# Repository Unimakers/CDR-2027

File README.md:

# Coupe de France de Robotique 2027 - Unimaker I1/I2

> [!IMPORTANT]
> Ce repo a été créé depuis le template de projet du MakerSpace d'Amiens.
> Les guides d'utilisation du template sont sur le
> [site de documentation du MakerSpace](https://doc.makerspace-amiens.fr/workshops/methodologie-de-projet/).

Ce repo est un site de documentation réalisé par l'équipe des première et deusième années pré-ingénieur de l'école Unilasalle-Amiens, membre de l'association de robotique Unimaker, dans le cadre de leur participation à la Coupe de France de Robotique 2027 (CDR 2027).
Cette documentation sera mise à jour tout au long de l'année à chaque étape du projet.

- **Documentation :** [site du projet](https://unimakers.fr/CDR-2027/) (sources dans [`docs/`](docs/))
- **Fichiers du projet :** [`project/`](project/) (CAO, électronique, code)

## Équipe

### Étudiants de deuxième année

- Ajaz Agbetiafa
- Baptiste Houzelot
- Brett Legret
- Emma Vilain
- Emrick Petit
- Enzo Deviliers
- Gauthier Henriques
- Martin Milon
- Paul Lapeyronnie
- Romain Vantalon
- Samuel Simao

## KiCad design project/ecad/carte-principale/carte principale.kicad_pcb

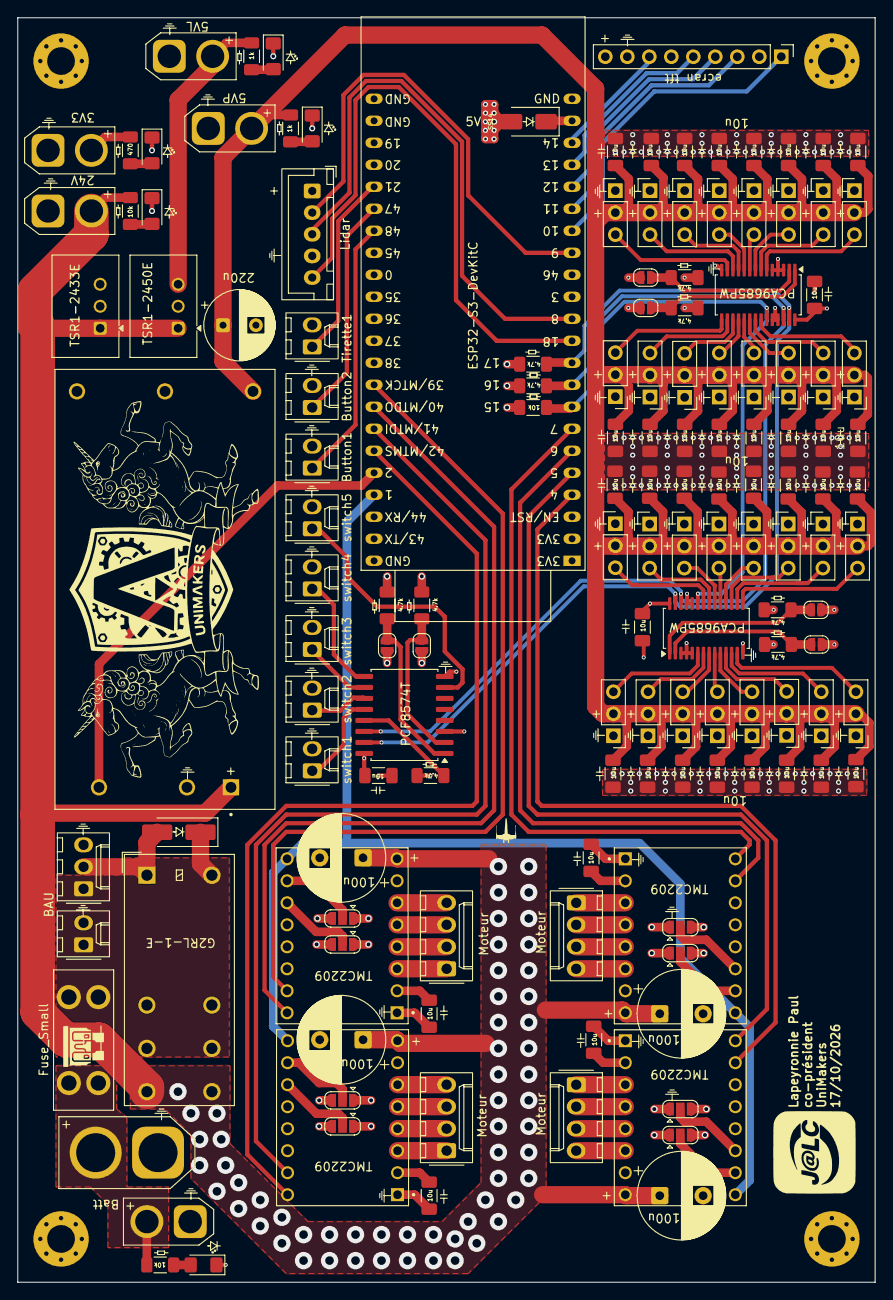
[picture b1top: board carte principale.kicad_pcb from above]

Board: 4 copper layers, 99.0 x 146.0 mm, 151 parts (0 on the bottom side), 106 nets.

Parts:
BAU: Conn_01x02; Molex_KK-254_AE-6410-02A_1x02_P2.54mm_Vertical
Batt: XT60; AMASS_XT60-M_1x02_P7.20mm_Vertical
Button1, Button2: Conn_01x02; Molex_KK-254_AE-6410-02A_1x02_P2.54mm_Vertical
C5, C6, C7, C9: 100u; CP_Radial_D10.0mm_P5.00mm
C12, C13, C14, C16, C17, C18, C19, C21, C22, C24, C25, C26, C27, C28, C29, C30, C31, C32, C33, C34, C35, C36, C37, C38, C39, C40, C41, C42, C43, C44, C45, C46, C47, C48, C49, C50, C51, C52, C53: 10u; C_1206_3216Metric_Pad1.33x1.80mm_HandSolder
C15: 220uF; CP_Radial_D8.0mm_P3.80mm
D1: SS14; D_SMA
D6: D_Small; D_SMA_Handsoldering
DT6, DT8, DT9, DT10, DT11: LED_Small; LED_1206_3216Metric_Pad1.42x1.75mm_HandSolder
F2: Fuse_Small; Fuseholder_Blade_Mini_Keystone_3568
H1, H2, H3, H4: M3; MountingHole_3.2mm_M3_Pad_Via
ICM1: PCF8574T; SOIC-16W_7.5x10.3mm_P1.27mm
J1: ecran tft; PinHeader_1x09_P2.54mm_Vertical
J4, J7, J8, J10: Conn_01x04; Molex_KK-254_AE-6410-04A_1x04_P2.54mm_Vertical
J5: LIDAR; JST_XH_B5B-XH-A_1x05_P2.50mm_Vertical
J6: BAU; Molex_KK-254_AE-6410-03A_1x03_P2.54mm_Vertical
JP1, JP2, JP3, JP4, JP5, JP6, JP16, JP19: SolderJumper_3_Open; SolderJumper-3_P1.3mm_Open_RoundedPad1.0x1.5mm
JP8, JP9, JP10, JP11, JP12, JP13: SolderJumper_2_Open; SolderJumper-2_P1.3mm_Open_RoundedPad1.0x1.5mm
K2: G2RL-1-E; Relay_SPDT_Omron_G2RL-1-E
PS1: TEN_50-2411; CONV_TEN_50-2411
R13, R15, R45: 10k; R_1206_3216Metric_Pad1.30x1.75mm_HandSolder
R14: 470; R_1206_3216Metric_Pad1.30x1.75mm_HandSolder
R16, R17: 1k; R_1206_3216Metric_Pad1.30x1.75mm_HandSolder
R31, R32, R33, R34, R35, R36, R37, R43, R44: 4.7k; R_1206_3216Metric_Pad1.30x1.75mm_HandSolder
Servo1, Servo2, Servo3, Servo4, Servo5, Servo6, Servo7, Servo8, Servo9, Servo10, Servo11, Servo12, Servo13, Servo14, Servo15, Servo16, Servo17, Servo18, Servo19, Servo20, Servo21, Servo22, Servo23, Servo24, Servo25, Servo26, Servo27, Servo28, Servo29, Servo30, Servo31, Servo32: PinHeader_1x03_P2.54mm_Vertical
Tirette1: Conn_01x02; Molex_KK-254_AE-6410-02A_1x02_P2.54mm_Vertical
U1: TSR1-2433E; Converter_DCDC_TRACO_TSR1-xxxxE_THT
U2: TSR1-2450E; Converter_DCDC_TRACO_TSR1-xxxxE_THT
U3, U11: PCA9685PW; TSSOP-28_4.4x9.7mm_P0.65mm
U4: ESP32-S3-DevKitC
U5, U6, U8, U9: TMC2209; MODULE_TMC2209_SILENTSTEPSTICK
XT30_3V3, XT30_5VL1, XT30_5VP1, XT30_24V1, XT30_BATT1: Conn_01x02; AMASS_XT30U-M_1x02_P5.0mm_Vertical
switch1, switch2, switch3, switch4, switch5: Conn_01x02; Molex_KK-254_AE-6410-02A_1x02_P2.54mm_Vertical

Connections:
+3V3: C12.1, C16.1, C18.1, C19.1, C21.1, C22.1, C53.1, ICM1.16 (VDD), J1.2, J1.6, JP1.3 (B), JP2.3 (B), JP3.3 (B), JP4.3 (B), JP5.3 (B), JP6.3 (B), JP8.1 (A), JP9.1 (A), JP10.1 (A), JP11.1 (A), JP12.1 (A), JP13.1 (A), JP16.3 (B), JP19.3 (B), R14.1, R37.1, R43.1, R44.1, R45.1, U1.3 (Vout), U3.28 (VDD), U5.2 (VIO), U6.2 (VIO), U8.2 (VIO), U9.2 (VIO), U11.28 (VDD), XT30_3V3.2
+5VL: D1.2 (A), J1.9, J5.1, R16.1, U2.3 (Vout), XT30_5VL1.2
+5VP: C13.1, C14.1, C15.1, C17.1, C24.1, C25.1, C26.1, C27.1, C28.1, C29.1, C30.1, C31.1, C32.1, C33.1, C34.1, C35.1, C36.1, C37.1, C38.1, C39.1, C40.1, C41.1, C42.1, C43.1, C44.1, C45.1, C46.1, C47.1, C48.1, C49.1, C50.1, C51.1, C52.1, PS1.4 (+VOUT), R17.1, Servo1.2, Servo2.2, Servo3.2, Servo4.2, Servo5.2, Servo6.2, Servo7.2, Servo8.2, Servo9.2, Servo10.2, Servo11.2, Servo12.2, Servo13.2, Servo14.2, Servo15.2, Servo16.2, Servo17.2, Servo18.2, Servo19.2, Servo20.2, Servo21.2, Servo22.2, Servo23.2, Servo24.2, Servo25.2, Servo26.2, Servo27.2, Servo28.2, Servo29.2, Servo30.2, Servo31.2, Servo32.2, XT30_5VP1.2
+24V: C5.1, C6.1, C7.1, C9.1, K2.14, PS1.1 (+VIN(VCC)), R15.1, U1.1 (Vin), U2.1 (Vin), U5.8 (VM), U6.8 (VM), U8.8 (VM), U9.8 (VM), XT30_24V1.2
+BATT: Batt.2, F2.1, R13.1, XT30_BATT1.2
/En driver: U4.41 (GPIO1/ADC1_CH0), U5.16 (~EN), U6.16 (~EN), U8.16 (~EN), U9.16 (~EN)
/RX: J5.3, U4.12 (GPIO8/ADC1_CH7)
/TX: J5.2, U4.15 (GPIO9/ADC1_CH8)
/bu 1: Button1.1, U4.29 (GPIO48)
/bu 2: Button2.1, U4.28 (GPIO47)
/cs: J1.7, U4.20 (GPIO14/ADC2_CH3)
/dc: J1.5, U4.19 (GPIO13/ADC2_CH2)
/oe: R45.2, U3.23 (~OE), U4.8 (GPIO15/ADC2_CH4/32K_P), U11.23 (~OE)
/pwm: J5.5, U4.11 (GPIO18/ADC2_CH7)
/sck: J1.3, U4.17 (GPIO11/ADC2_CH0)
/sdi: J1.4, U4.18 (GPIO12/ADC2_CH1)
/sdo: J1.1, U4.16 (GPIO10/ADC1_CH9)
/sw1: ICM1.12 (P7), switch1.1
/sw2: ICM1.11 (P6), switch2.1
/sw3: ICM1.10 (P5), switch3.1
/sw4: ICM1.9 (P4), switch4.1
/sw5: ICM1.7 (P3), switch5.1
/tir: Tirette1.1 (Pin_1_1), U4.27 (GPIO21)
DIR 1: U4.39 (GPIO42/MTMS), U5.9 (DIR)
DIR 2: U4.5 (GPIO5/ADC1_CH4), U6.9 (DIR)
DIR 3: U4.37 (GPIO40/MTDO), U8.9 (DIR)
DIR 4: U4.7 (GPIO7/ADC1_CH6), U9.9 (DIR)
En5VP: PS1.3 (ON/OFF), U4.40 (GPIO2/ADC1_CH1)
GND: BAU.2, Batt.1, Button1.2, Button2.2, C5.2, C6.2, C7.2, C9.2, C12.2, C13.2, C14.2, C15.2, C16.2, C17.2, C18.2, C19.2, C21.2, C22.2, C24.2, C25.2, C26.2, C27.2, C28.2, C29.2, C30.2, C31.2, C32.2, C33.2, C34.2, C35.2, C36.2, C37.2, C38.2, C39.2, C40.2, C41.2, C42.2, C43.2, C44.2, C45.2, C46.2, C47.2, C48.2, C49.2, C50.2, C51.2, C52.2, C53.2, DT6.1 (K), DT8.1 (K), DT9.1 (K), DT10.1 (K), DT11.1 (K), H1.1 (1_1), H2.1 (1_1), H3.1 (1_1), H4.1 (1_1), ICM1.3 (A2), ICM1.8 (GND), J1.8, J5.4, J6.3, JP1.1 (A), JP2.1 (A), JP3.1 (A), JP4.1 (A), JP5.1 (A), JP6.1 (A), JP16.1 (A), JP19.1 (A), PS1.2 (-VIN(GND)), PS1.5 (-VOUT), R31.2, R32.2, R33.2, R34.2, R35.2, R36.2, Servo1.1, Servo2.1, Servo3.1, Servo4.1, Servo5.1, Servo6.1, Servo7.1, Servo8.1, Servo9.1, Servo10.1, Servo11.1, Servo12.1, Servo13.1, Servo14.1, Servo15.1, Servo16.1, Servo17.1, Servo18.1, Servo19.1, Servo20.1, Servo21.1, Servo22.1, Servo23.1, Servo24.1, Servo25.1, Servo26.1, Servo27.1, Servo28.1, Servo29.1, Servo30.1, Servo31.1, Servo32.1, U1.2 (GND), U2.2 (GND), U3.3 (A2), U3.4 (A3), U3.5 (A4), U3.14 (VSS), U3.24 (A5), U3.25 (EXTCLK), U4.22 (GND), U4.23 (GND), U4.24 (GND), U4.44 (GND), U5.1 (GND), U5.7 (GND), U6.1 (GND), U6.7 (GND), U8.1 (GND), U8.7 (GND), U9.1 (GND), U9.7 (GND), U11.3 (A2), U11.4 (A3), U11.5 (A4), U11.14 (VSS), U11.24 (A5), U11.25 (EXTCLK), XT30_3V3.1, XT30_5VL1.1, XT30_5VP1.1, XT30_24V1.1, XT30_BATT1.1, switch1.2, switch2.2, switch3.2, switch4.2, switch5.2
unnamed: BAU.1, D6.1 (K), F2.2, J6.1, K2.11, K2.A2
unnamed: D1.1 (K), U4.21 (5V)
unnamed: D6.2 (A), J6.2, K2.A1
unnamed: DT6.2 (A), R13.2
unnamed: DT8.2 (A), R15.2
unnamed: DT9.2 (A), R14.2
unnamed: DT10.2 (A), R16.2
unnamed: DT11.2 (A), R17.2
unnamed: ICM1.1 (A0), JP12.2 (B), R35.1
unnamed: ICM1.2 (A1), JP13.2 (B), R36.1
unnamed: ICM1.13 (~INT), R37.2
unnamed: J4.1, U5.3 (M1B)
unnamed: J4.2, U5.4 (M1A)
unnamed: J4.3, U5.5 (M2A)
unnamed: J4.4, U5.6 (M2B)
unnamed: J7.1, U6.3 (M1B)
unnamed: J7.2, U6.4 (M1A)
unnamed: J7.3, U6.5 (M2A)
unnamed: J7.4, U6.6 (M2B)
unnamed: J8.1, U8.3 (M1B)
unnamed: J8.2, U8.4 (M1A)
unnamed: J8.3, U8.5 (M2A)
unnamed: J8.4, U8.6 (M2B)
unnamed: J10.1, U9.3 (M1B)
unnamed: J10.2, U9.4 (M1A)
unnamed: J10.3, U9.5 (M2A)
unnamed: J10.4, U9.6 (M2B)
unnamed: JP1.2 (C), U5.15 (MS1)
unnamed: JP2.2 (C), U5.14 (MS2)
unnamed: JP3.2 (C), U6.15 (MS1)
unnamed: JP4.2 (C), U8.15 (MS1)
unnamed: JP5.2 (C), U8.14 (MS2)
unnamed: JP6.2 (C), U9.15 (MS1)
unnamed: JP8.2 (B), R32.1, U3.1 (A0)
unnamed: JP9.2 (B), R31.1, U3.2 (A1)
unnamed: JP10.2 (B), R33.1, U11.1 (A0)
unnamed: JP11.2 (B), R34.1, U11.2 (A1)
unnamed: JP16.2 (C), U6.14 (MS2)
unnamed: JP19.2 (C), U9.14 (MS2)
unnamed: Servo1.3, U3.7 (LED1)
unnamed: Servo2.3, U3.9 (LED3)
unnamed: Servo3.3, U3.11 (LED5)
unnamed: Servo4.3, U3.13 (LED7)
unnamed: Servo5.3, U3.6 (LED0)
unnamed: Servo6.3, U3.8 (LED2)
unnamed: Servo7.3, U3.10 (LED4)
unnamed: Servo8.3, U3.12 (LED6)
unnamed: Servo9.3, U3.16 (LED9)
unnamed: Servo10.3, U3.18 (LED11)
unnamed: Servo11.3, U3.20 (LED13)
unnamed: Servo12.3, U3.22 (LED15)
unnamed: Servo13.3, U3.15 (LED8)
unnamed: Servo14.3, U3.17 (LED10)
unnamed: Servo15.3, U3.19 (LED12)
unnamed: Servo16.3, U3.21 (LED14)
unnamed: Servo17.3, U11.7 (LED1)
unnamed: Servo18.3, U11.9 (LED3)
unnamed: Servo19.3, U11.11 (LED5)
unnamed: Servo20.3, U11.13 (LED7)
unnamed: Servo21.3, U11.16 (LED9)
unnamed: Servo22.3, U11.18 (LED11)
unnamed: Servo23.3, U11.20 (LED13)
unnamed: Servo24.3, U11.22 (LED15)
unnamed: Servo25.3, U11.6 (LED0)
unnamed: Servo26.3, U11.8 (LED2)
unnamed: Servo27.3, U11.10 (LED4)
unnamed: Servo28.3, U11.12 (LED6)
unnamed: Servo29.3, U11.15 (LED8)
unnamed: Servo30.3, U11.17 (LED10)
unnamed: Servo31.3, U11.19 (LED12)
unnamed: Servo32.3, U11.21 (LED14)
SCL: ICM1.14 (SCL), R43.2, U3.26 (SCL), U4.9 (GPIO16/ADC2_CH5/32K_N), U11.26 (SCL)
SDA: ICM1.15 (SDA), R44.2, U3.27 (SDA), U4.10 (GPIO17/ADC2_CH6), U11.27 (SDA)
STEP 1: U4.38 (GPIO41/MTDI), U5.10 (STEP)
STEP 2: U4.4 (GPIO4/ADC1_CH3), U6.10 (STEP)
STEP 3: U4.36 (GPIO39/MTCK), U8.10 (STEP)
STEP 4: U4.6 (GPIO6/ADC1_CH5), U9.10 (STEP)

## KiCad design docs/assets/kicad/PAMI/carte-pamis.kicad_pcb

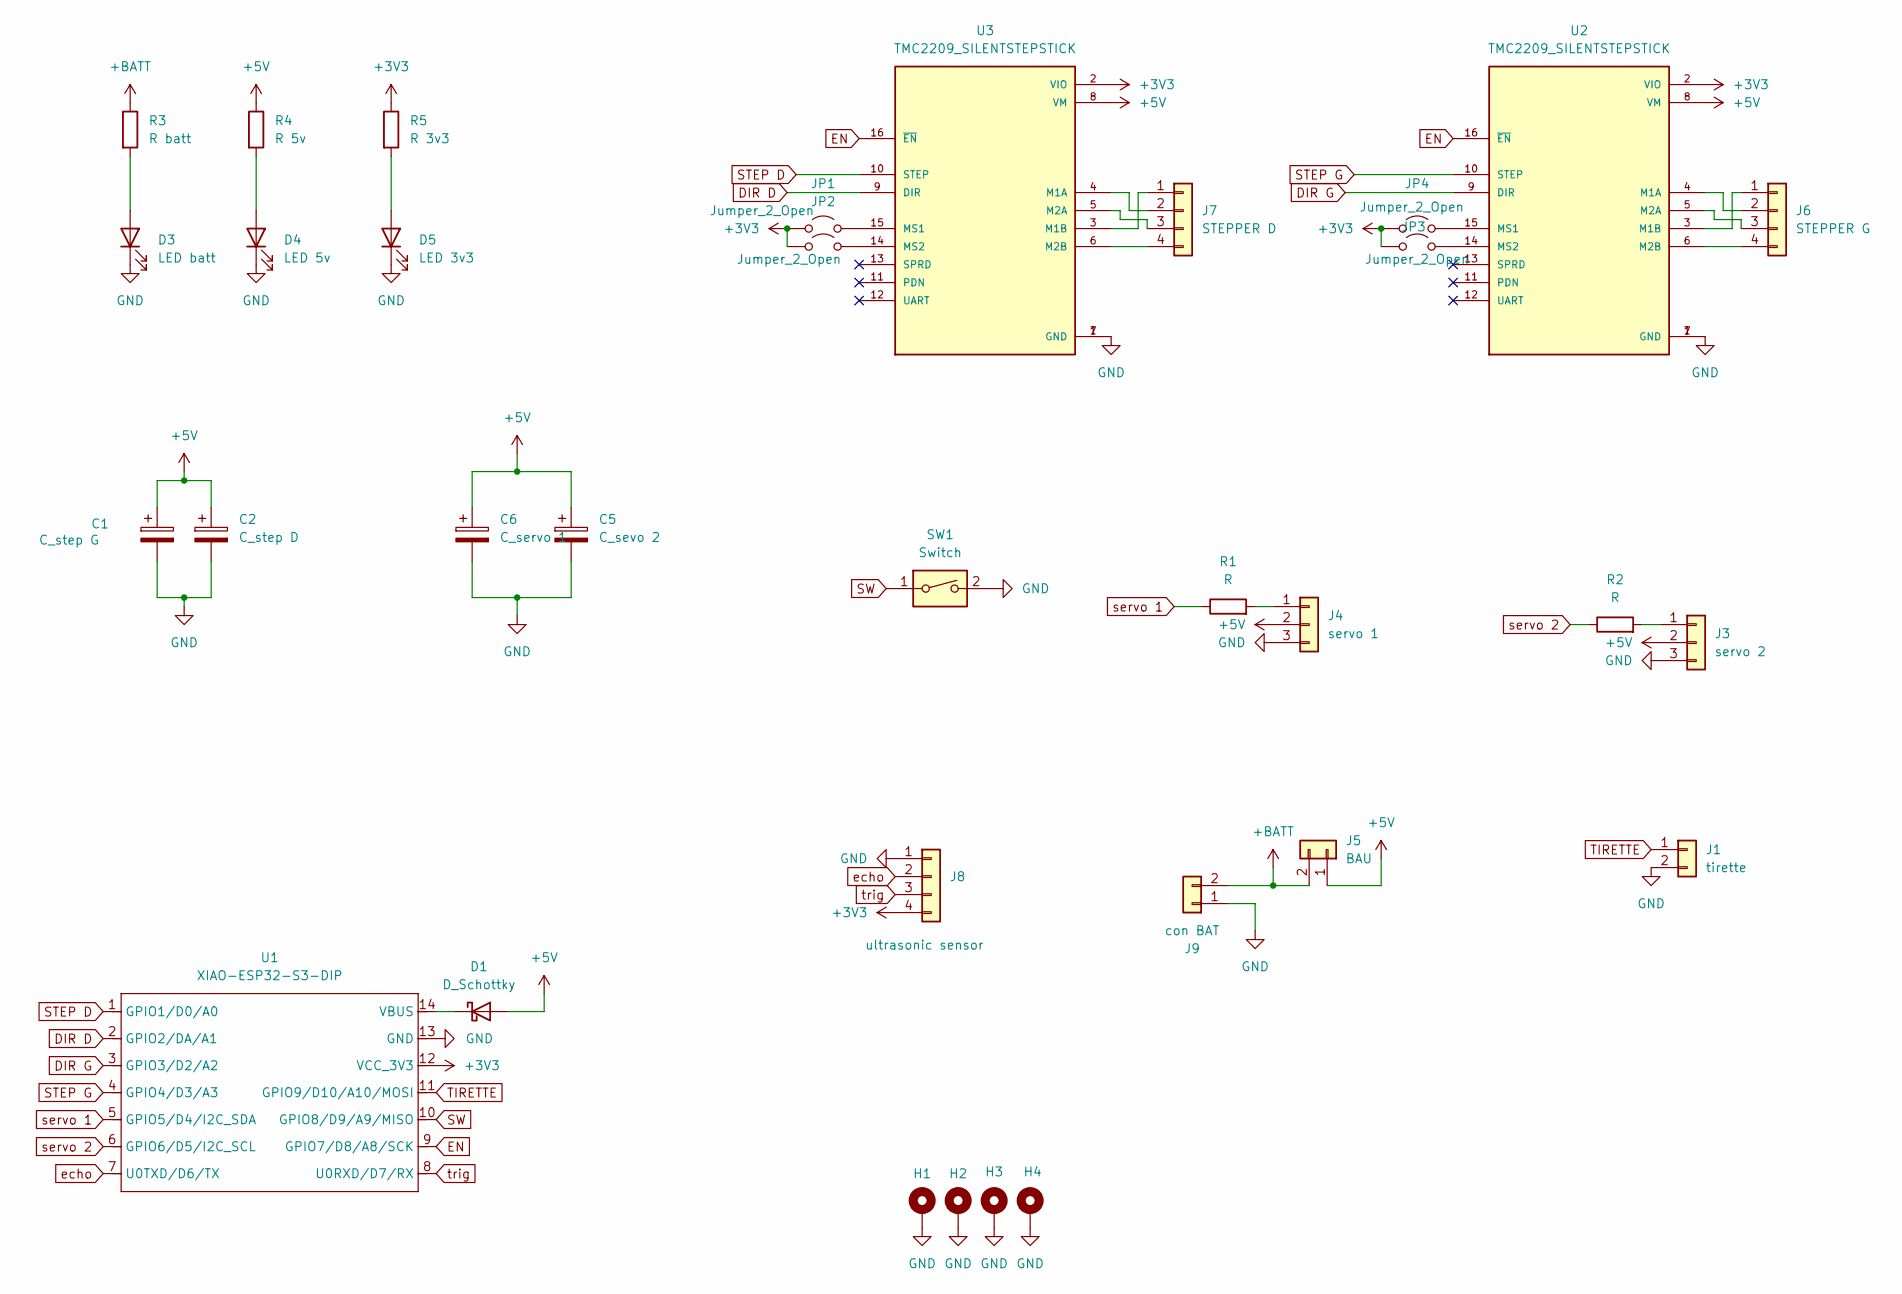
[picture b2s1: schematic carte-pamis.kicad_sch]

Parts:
C1: C_step G; CP_Radial_D6.3mm_P2.50mm
C2: C_step D; CP_Radial_D6.3mm_P2.50mm
C5: C_sevo 2; CP_Radial_D6.3mm_P2.50mm
C6: C_servo 1; CP_Radial_D6.3mm_P2.50mm
D1: D_Schottky; D_A-405_P10.16mm_Horizontal
D3: LED batt; LED_1206_3216Metric_Pad1.42x1.75mm_HandSolder
D4: LED 5v; LED_1206_3216Metric_Pad1.42x1.75mm_HandSolder
D5: LED 3v3; LED_1206_3216Metric_Pad1.42x1.75mm_HandSolder
H1, H2, H3, H4: MountingHole_Pad; MountingHole_3.2mm_M3_Pad_Via
J1: tirette; Molex_KK-254_AE-6410-02A_1x02_P2.54mm_Vertical
J3: servo 2; PinHeader_1x03_P2.54mm_Vertical
J4: servo 1; PinHeader_1x03_P2.54mm_Vertical
J5: BAU; Molex_KK-396_A-41791-0002_1x02_P3.96mm_Vertical
J6: STEPPER G; Molex_KK-254_AE-6410-04A_1x04_P2.54mm_Vertical
J7: STEPPER D; Molex_KK-254_AE-6410-04A_1x04_P2.54mm_Vertical
J8: ultrasonic sensor; PinSocket_1x04_P2.54mm_Vertical
J9: con BAT; AMASS_XT30U-M_1x02_P5.0mm_Vertical
JP1, JP2, JP3, JP4: Jumper_2_Open; SolderJumper-2_P1.3mm_Open_RoundedPad1.0x1.5mm
R1: R; R_1206_3216Metric_Pad1.30x1.75mm_HandSolder
R2: R; C_1206_3216Metric_Pad1.33x1.80mm_HandSolder
R3: R batt; R_1206_3216Metric_Pad1.30x1.75mm_HandSolder
R4: R 5v; R_1206_3216Metric_Pad1.30x1.75mm_HandSolder
R5: R 3v3; R_1206_3216Metric_Pad1.30x1.75mm_HandSolder
SW1: Switch; SW_DIP_SPSTx01_Slide_9.78x4.72mm_W7.62mm_P2.54mm
U1: XIAO-ESP32-S3-DIP; XIAO-ESP32S3-DIP
U2, U3: TMC2209_SILENTSTEPSTICK; MODULE_TMC2209_SILENTSTEPSTICK; PARTREV 1.20

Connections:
+3V3: J8.4, JP1.1 (A), JP2.1 (A), JP3.1 (A), JP4.1 (A), R5.1, U1.12 (VCC_3V3), U2.2 (VIO), U3.2 (VIO)
+5V: C1.1, C2.1, C5.1, C6.1, D1.2 (A), J3.2, J4.2, J5.1, R4.1, U2.8 (VM), U3.8 (VM)
+BATT: J5.2, J9.2, R3.1
DIR D: U1.2 (GPIO2/DA/A1), U3.9 (DIR)
DIR G: U1.3 (GPIO3/D2/A2), U2.9 (DIR)
EN: U1.9 (GPIO7/D8/A8/SCK), U2.16 (~EN), U3.16 (~EN)
GND: C1.2, C2.2, C5.2, C6.2, D3.1 (K), D4.1 (K), D5.1 (K), H1.1, H2.1, H3.1, H4.1, J1.2, J3.3, J4.3, J8.1, J9.1, SW1.2, U1.13 (GND), U2.1 (GND), U2.7 (GND), U3.1 (GND), U3.7 (GND)
unnamed: D1.1 (K), U1.14 (VBUS)
unnamed: D3.2 (A), R3.2
unnamed: D4.2 (A), R4.2
unnamed: D5.2 (A), R5.2
unnamed: J3.1, R2.2
unnamed: J4.1, R1.2
unnamed: J6.1, U2.3 (M1B)
unnamed: J6.2, U2.4 (M1A)
unnamed: J6.3, U2.5 (M2A)
unnamed: J6.4, U2.6 (M2B)
unnamed: J7.1, U3.3 (M1B)
unnamed: J7.2, U3.4 (M1A)
unnamed: J7.3, U3.5 (M2A)
unnamed: J7.4, U3.6 (M2B)
unnamed: JP1.2 (B), U3.15 (MS1)
unnamed: JP2.2 (B), U3.14 (MS2)
unnamed: JP3.2 (B), U2.14 (MS2)
unnamed: JP4.2 (B), U2.15 (MS1)
STEP D: U1.1 (GPIO1/D0/A0), U3.10 (STEP)
STEP G: U1.4 (GPIO4/D3/A3), U2.10 (STEP)
SW: SW1.1, U1.10 (GPIO8/D9/A9/MISO)
TIRETTE: J1.1, U1.11 (GPIO9/D10/A10/MOSI)
echo: J8.2, U1.7 (U0TXD/D6/TX)
servo 1: R1.1, U1.5 (GPIO5/D4/I2C_SDA)
servo 2: R2.1, U1.6 (GPIO9/D5/I2C_SCL)
trig: J8.3, U1.8 (U0RXD/D7/RX)

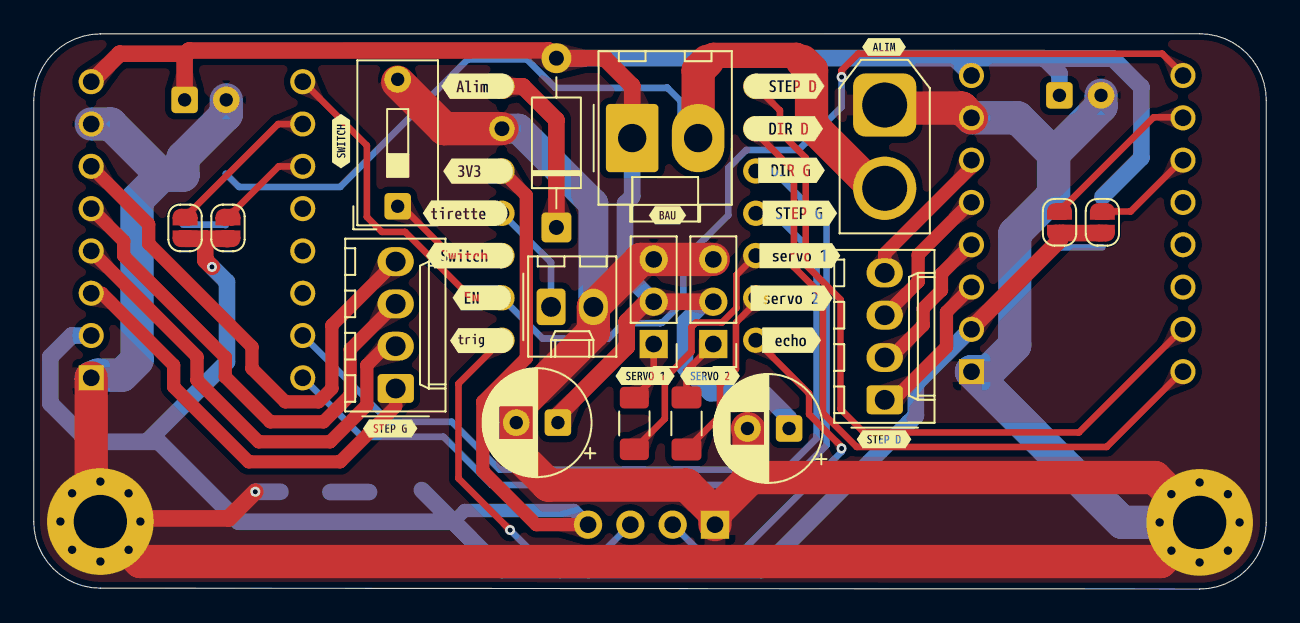
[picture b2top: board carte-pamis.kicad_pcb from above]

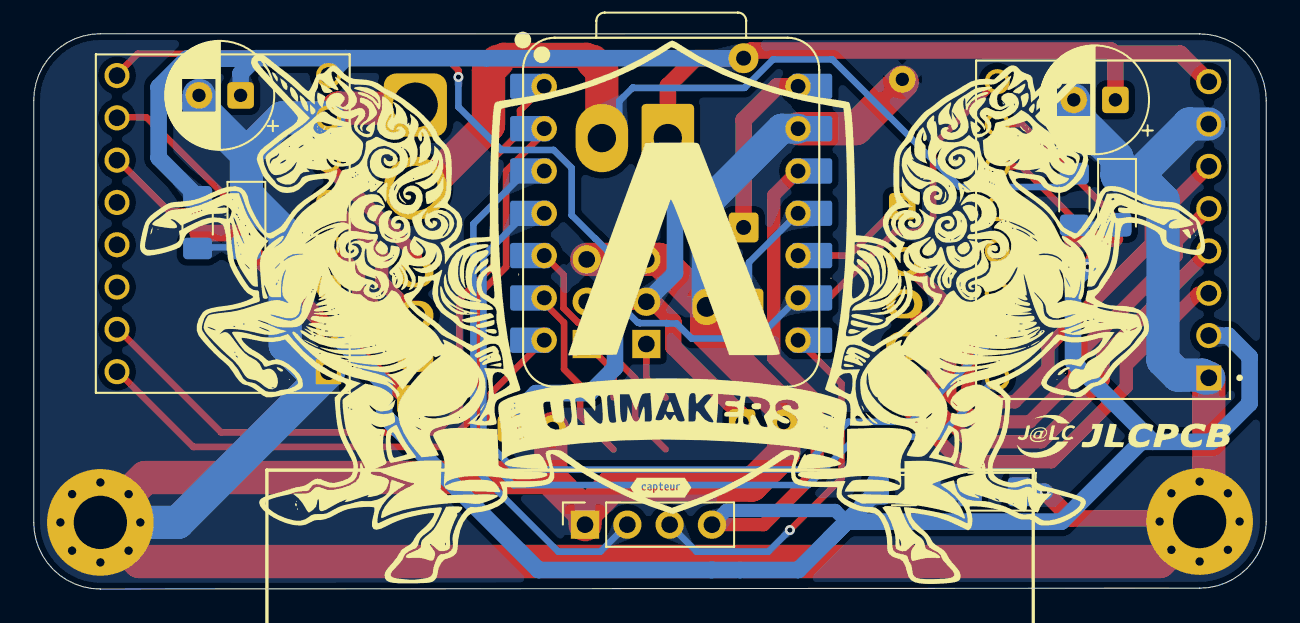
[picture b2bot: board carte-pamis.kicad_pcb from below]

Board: 2 copper layers, 74.0 x 33.3 mm, 52 parts (13 on the bottom side), 33 nets.

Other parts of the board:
kibuzzard-69BD5A4D: G***; kibuzzard-69BD5A4D
kibuzzard-69BD5AEA: G***; kibuzzard-69BD5AEA
kibuzzard-69BD5B6A: G***; kibuzzard-69BD5B6A
kibuzzard-69BD5B57: G***; kibuzzard-69BD5B57
kibuzzard-69BD5B92: G***; kibuzzard-69BD5B92
kibuzzard-69BD5BD3: G***; kibuzzard-69BD5BD3
kibuzzard-69BD5C33: G***; kibuzzard-69BD5C33
kibuzzard-69BD5DD3: G***; kibuzzard-69BD5DD3
kibuzzard-69C3F8DE: G***; kibuzzard-69C3F8DE
kibuzzard-69C3F80C: G***; kibuzzard-69C3F80C
kibuzzard-69C3F81F: G***; kibuzzard-69C3F81F
kibuzzard-69C3F82B: G***; kibuzzard-69C3F82B
kibuzzard-69C3F838: G***; kibuzzard-69C3F838
kibuzzard-69C3F846: G***; kibuzzard-69C3F846
kibuzzard-69C4E0EF: G***; kibuzzard-69C4E0EF
kibuzzard-69C4E14F: G***; kibuzzard-69C4E14F
kibuzzard-69C402F1: G***; kibuzzard-69C402F1
kibuzzard-69C403F5: G***; kibuzzard-69C403F5
kibuzzard-69C4034C: G***; kibuzzard-69C4034C
kibuzzard-69C40313: G***; kibuzzard-69C40313
kibuzzard-69C40336: G***; kibuzzard-69C40336

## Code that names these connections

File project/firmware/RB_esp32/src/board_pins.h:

// Board pinout: exact mirror of the KiCad project ECAD-2026 "body v1"
// (Seeed XIAO ESP32-S3 Plus = X1), its two driver boards "leg v1" (2x TMC2209 each,
// plugged on NP1 and NP2) and the head board "head v1" (plugged on NP3).
// Checked against the PCB nets (body v1.kicad_pcb, carte driver.kicad_pcb).
// Only edit this file when a PCB changes. What each slot is USED for lives in robot_config.h.

#pragma once

#include <stdint.h>

// ---------------------------------------------------------------------------
// I2C bus: PCF8574 of the body (drivers), PCF8574 of the head (switches),
// external PCA9685 modules on the 4 I2C connectors IC1..IC4.
// 4.7k pull-ups to 3V3 on the body (R5, R6) and on the head (R7, R8).
// The PCF8574 is a 100 kHz (standard mode) chip: keep the Wire default clock.
// ---------------------------------------------------------------------------
#define I2C_SDA_PIN 5 // D4
#define I2C_SCL_PIN 6 // D5

// ---------------------------------------------------------------------------
// Stepper drivers: 2 driver boards "leg v1", 2 TMC2209 each, 24V, STEP/DIR on the XIAO,
// ~EN and microstepping (MS1/MS2) on the body PCF8574. UART, DIAG, INDEX not wired.
//
//   slot | body conn. | driver board | motor connector | 2026 robot use
//   -----+------------+--------------+-----------------+---------------
//     0  |    NP1     |  U1          |  J3             | back elevator
//     1  |    NP1     |  U2          |  J2             | LEFT wheel
//     2  |    NP2     |  U1          |  J3             | front elevator
//     3  |    NP2     |  U2          |  J2             | RIGHT wheel
//
// WARNING: on the driver board the nets "STEP 1" and "DIR 1" are swapped on U1
// (net "STEP 1" goes to the DIR pad 9, net "DIR 1" to the STEP pad 10). U2 is right.
// The pins below are the REAL function at the TMC2209, so the swap is already corrected:
// slot 0 STEP = net "DIR 1" (GPIO4), slot 2 STEP = net "DIR 3" (GPIO2).
// (The 2026 firmware used the net names, STEP = GPIO3 / GPIO1, for the elevators: if an
// elevator does not move, swap STEP_1/DIR_1 or STEP_3/DIR_3 here. The wheels are on U2,
// not affected, and their pins are the ones validated in 2026.)
// ---------------------------------------------------------------------------
#define STEPPER_SLOT_COUNT 4

#define STEP_1_PIN 4  // net "DIR 1"  (D3)   -> NP1 U1 STEP
#define DIR_1_PIN 3   // net "STEP 1" (D2)   -> NP1 U1 DIR
#define STEP_2_PIN 40 // net "STEP 2" (D13)  -> NP1 U2 STEP
#define DIR_2_PIN 10  // net "DIR 2"  (D16)  -> NP1 U2 DIR
#define STEP_3_PIN 2  // net "DIR 3"  (D1)   -> NP2 U1 STEP
#define DIR_3_PIN 1   // net "STEP 3" (D0)   -> NP2 U1 DIR
#define STEP_4_PIN 38 // net "STEP 4" (D11)  -> NP2 U2 STEP
#define DIR_4_PIN 39  // net "DIR 4"  (D12)  -> NP2 U2 DIR

// Driver board of each slot: both TMC2209 of a board share ~EN, MS1 and MS2.
#define DRIVER_BOARD_COUNT 2
const uint8_t STEPPER_SLOT_BOARD[STEPPER_SLOT_COUNT] = {0, 0, 1, 1}; // slot -> board (0 = NP1, 1 = NP2)

// ---------------------------------------------------------------------------
// PCF8574T ICM1 on the body: ~EN and MS1/MS2 of the 2 driver boards.
// Address = 0x20 + (A2 A1 A0) for a PCF8574T (0x38 + ... would be a PCF8574AT).
// A0..A2 have a pull-down (R1..R3) and a solder jumper to 3V3 (JP1..JP3): 0x20 with no jumper.
// ~INT has a 4.7k pull-up (R4) but is not wired to the XIAO.
//
// At power-on every PCF pin is HIGH (weak pull-up): ~EN = 1 -> drivers disabled,
// MS1 = MS2 = 1 -> 1/16 microstep, until steppersBegin() writes the real values.
//
//   PCF bit | NP pin | driver board signal
//   --------+--------+--------------------
//     P3    | NP1-1  | board 0 ~EN
//     P2    | NP1-2  | board 0 MS1
//     P1    | NP1-3  | (not connected on the driver board)
//     P0    | NP1-4  | board 0 MS2
//     P4    | NP2-1  | board 1 ~EN
//     P5    | NP2-2  | board 1 MS1
//     P6    | NP2-3  | (not connected on the driver board)
//     P7    | NP2-4  | board 1 MS2
// ---------------------------------------------------------------------------
#define PCF_DRIVERS_ADDR 0x20

const uint8_t DRIVER_EN_PCF_BIT[DRIVER_BOARD_COUNT] = {3, 4};
const uint8_t DRIVER_MS1_PCF_BIT[DRIVER_BOARD_COUNT] = {2, 5};
const uint8_t DRIVER_MS2_PCF_BIT[DRIVER_BOARD_COUNT] = {0, 7};
#define DRIVERS_EN_ACTIVE_LOW true

// TMC2209 standalone microstepping (MS1 / MS2 levels):
//   MS1=0 MS2=0 -> 8   |   MS1=1 MS2=0 -> 2   |   MS1=0 MS2=1 -> 4   |   MS1=1 MS2=1 -> 16

// ---------------------------------------------------------------------------
// Power
// ---------------------------------------------------------------------------
#define EN_5VP_PIN 13 // "En5VP" (D17): ON/OFF of the 5VP converter PS1 (servos/pumps)

// ---------------------------------------------------------------------------
// PCA9685 PWM drivers: no longer on the body, external modules on the I2C
// connectors IC1..IC4. Address = 0x40 + jumpers of the module.
// 0x70 is the PCA9685 "all call" address (enabled at power-on): never give it to a chip.
// ---------------------------------------------------------------------------
#define PCA_COUNT 2
#define PCA_CHANNEL_COUNT 16 // outputs per PCA9685

#define PCA_1_ADDR 0x40
#define PCA_2_ADDR 0x41

// ~OE of the PCA modules is not wired to the XIAO (module pull-down = outputs on)
#define PCA_OE_PIN -1

static_assert(PCA_1_ADDR == -1 || PCA_2_ADDR == -1 || PCA_1_ADDR != PCA_2_ADDR,
              "Both PCA9685 have the same I2C address, check the module jumpers");
static_assert(PCA_1_ADDR != 0x70 && PCA_2_ADDR != 0x70,
              "0x70 is the PCA9685 all-call address, choose another one");

// Actuator "connectors" 1..32 = PCA 1 outputs 0..15 then PCA 2 outputs 0..15
// (straight mapping on the external modules, unlike the interleaved old main board).
#define ACTUATOR_CONNECTOR_COUNT (PCA_COUNT * PCA_CHANNEL_COUNT)
const uint8_t ACTUATOR_PCA_CHANNEL[PCA_CHANNEL_COUNT] = {0, 1, 2, 3, 4, 5, 6, 7, 8, 9, 10, 11, 12, 13, 14, 15};

// ---------------------------------------------------------------------------
// Head board (NP3 "IHM + Lidar"): PCF8574T ICM1 with 4 switch connectors J1..J4.
// Same chip and same jumper circuit as the body PCF: with no jumper BOTH PCF answer
// on 0x20 and the bus does not work. Solder JP1 (A0) on the head -> 0x21.
// Switch contact to GND. Quasi-bidirectional pins: write 1 before reading, closed = 0.
// P4..P7 are not connected.
// ---------------------------------------------------------------------------
#define PCF_HEAD_ADDR 0x21

#define SWITCH_COUNT 4
const uint8_t SWITCH_PCF_BIT[SWITCH_COUNT] = {0, 1, 2, 3}; // J1..J4 -> P0..P3

static_assert(PCF_DRIVERS_ADDR != PCF_HEAD_ADDR,
              "Both PCF8574 have the same I2C address: solder JP1 on the head board");
static_assert(PCF_DRIVERS_ADDR != PCA_1_ADDR && PCF_DRIVERS_ADDR != PCA_2_ADDR &&
              PCF_HEAD_ADDR != PCA_1_ADDR && PCF_HEAD_ADDR != PCA_2_ADDR,
              "A PCF8574 shares its I2C address with a PCA9685");

// ---------------------------------------------------------------------------
// Inputs on the XIAO, through the head board (contact to GND: use INPUT_PULLUP)
// ---------------------------------------------------------------------------
#define TIRETTE_PIN 12     // "tir" (D18), head J6
#define TEAM_SWITCH_PIN 11 // "TSW" (D19), head J7

// ---------------------------------------------------------------------------
// WS2812B RGB LEDs on the head (D11 -> D12 chained), 5VL powered
// ---------------------------------------------------------------------------
#define RGB_LED_PIN 7 // "LED" (D8)
#define RGB_LED_COUNT 2

// ---------------------------------------------------------------------------
// LIDAR LD06 on head J5, UART1 on the XIAO hardware UART pins.
// Serial = native USB CDC on the XIAO, so GPIO43/44 are free for the lidar.
// Always pass the pins: Serial1.begin(LD06_BAUDRATE, SERIAL_8N1, LD06_RX_PIN, LD06_TX_PIN),
// and never call LD06::init(), which uses the defaults.
// ---------------------------------------------------------------------------
#define LD06_UART_NUM 1
// The nets are named from the lidar side: the LD06 data arrives on net "TX" (GPIO43).
// Same as Firmware-CDR2026-MainBot (LIDAR_RX_PIN = TX), validated on the 2026 robot.
#define LD06_RX_PIN 43 // net "TX" (D6): XIAO RX <- LD06 TX (head J5 pin 2)
#define LD06_TX_PIN 44 // net "RX" (D7): XIAO TX -> head J5 pin 3
#define LD06_BAUDRATE 230400
#define LD06_PWM_PIN 8 // "PWM" (D9): motor speed PWM, head J5 pin 5

// ---------------------------------------------------------------------------
// XBee (L1: DOUT, DIN, 3V3, GND) on UART2
// ---------------------------------------------------------------------------
#define XBEE_RX_PIN 41 // "DOUT-xbee" (D14): XIAO RX <- XBee DOUT
#define XBEE_TX_PIN 42 // "DIN-xbee"  (D15): XIAO TX -> XBee DIN

// Free: GPIO9 (D10)

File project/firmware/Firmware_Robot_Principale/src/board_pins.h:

// Board pinout: exact mirror of the final KiCad schematic "carte principale"
// (project/ecad/carte-principale, ESP32-S3-DevKitC-1 = U4).
// Only edit this file when the PCB changes. What each slot is USED for lives in robot_config.h.

#pragma once

#include <stdint.h>

// ---------------------------------------------------------------------------
// Stepper drivers (TMC2209 U5, U6, U8, U9, 24V, STEP/DIR only: UART, DIAG and INDEX not wired)
// Slot index used in robot_config.h = STEP/DIR number on the schematic - 1.
//
//   slot | driver | motor connector | microstep jumpers (MS1 / MS2)
//   -----+--------+-----------------+------------------------------
//     0  |   U5   |       J4        |   JP1 / JP2
//     1  |   U6   |       J7        |   JP3 / JP16
//     2  |   U8   |       J8        |   JP4 / JP5
//     3  |   U9   |       J10       |   JP6 / JP19
// ---------------------------------------------------------------------------
#define STEPPER_SLOT_COUNT 4

#define STEP_1_PIN 41
#define DIR_1_PIN 42
#define STEP_2_PIN 4
#define DIR_2_PIN 5
#define STEP_3_PIN 39
#define DIR_3_PIN 40
#define STEP_4_PIN 6
#define DIR_4_PIN 7

// Shared ~EN of the 4 drivers ("En driver"), active LOW. No pull resistor on the board:
// the line floats from power-on until steppersBegin() drives it.
#define MOTORS_EN_PIN 1
#define MOTORS_EN_ACTIVE_LOW true

// TMC2209 standalone microstepping, set by the solder jumpers (B = 3V3, A = GND):
//   MS1=0 MS2=0 -> 8   |   MS1=1 MS2=0 -> 2   |   MS1=0 MS2=1 -> 4   |   MS1=1 MS2=1 -> 16

// ---------------------------------------------------------------------------
// Power
// ---------------------------------------------------------------------------
#define EN_5VP_PIN 2 // ON/OFF of the 5VP converter PS1 (servos/pumps)

// ---------------------------------------------------------------------------
// I2C bus: the 2 PCA9685 and the PCF8574, 4.7k pull-ups to 3V3 on board (R43, R44)
// The PCF8574 is a 100 kHz (standard mode) chip: keep the Wire default clock, do not
// raise it with Wire.setClock() while the PCF8574 is on the bus.
// ---------------------------------------------------------------------------
#define I2C_SDA_PIN 17
#define I2C_SCL_PIN 16

// ---------------------------------------------------------------------------
// PCA9685 PWM drivers U3 and U11: signal only. The actuators get 5VP + GND from the board.
// ---------------------------------------------------------------------------
#define PCA_COUNT 2
#define PCA_CHANNEL_COUNT 16 // outputs per PCA9685

// Address = 0x40 + (A1 A0). A2..A5 are tied to GND; A0/A1 have a 4.7k pull-down
// and a solder jumper to 3V3. With no jumper soldered both chips answer on 0x40.
//   U3  (PCA 1): A0 = JP8,  A1 = JP9   -> 0x40 with no jumper
//   U11 (PCA 2): A0 = JP10, A1 = JP11  -> 0x41 with JP10 soldered
// 0x70 is the PCA9685 "all call" address (enabled at power-on): never give it to a chip.
#define PCA_1_ADDR 0x40
#define PCA_2_ADDR 0x41

// ~OE of both PCA, active LOW. 10k pull-up (R45): every output is off from
// power-on until actuatorsBegin() drives it LOW.
#define PCA_OE_PIN 15

static_assert(PCA_1_ADDR == -1 || PCA_2_ADDR == -1 || PCA_1_ADDR != PCA_2_ADDR,
              "Both PCA9685 have the same I2C address, check the solder jumpers");
static_assert(PCA_1_ADDR != 0x70 && PCA_2_ADDR != 0x70,
              "0x70 is the PCA9685 all-call address, choose another one");

// ---------------------------------------------------------------------------
// Actuator connectors "Servo1".."Servo32" (GND, 5VP, signal).
// Servo1..16 -> U3 (PCA 1), Servo17..32 -> U11 (PCA 2). Inside each group of 16
// the wiring is interleaved, identically on both chips:
//   connector in group : 1  2  3  4  5  6  7  8  9  10 11 12 13 14 15 16
//   PCA output (LEDx)  : 1  3  5  7  0  2  4  6  9  11 13 15 8  10 12 14
// For connector n (1..32): pca = (n - 1) / 16, output = ACTUATOR_PCA_CHANNEL[(n - 1) % 16]
// ---------------------------------------------------------------------------
#define ACTUATOR_CONNECTOR_COUNT (PCA_COUNT * PCA_CHANNEL_COUNT)
const uint8_t ACTUATOR_PCA_CHANNEL[PCA_CHANNEL_COUNT] = {1, 3, 5, 7, 0, 2, 4, 6, 9, 11, 13, 15, 8, 10, 12, 14};

// ---------------------------------------------------------------------------
// PCF8574T I/O expander ICM1: the 5 switch connectors "switch1".."switch5".
// Address = 0x38 + (A2 A1 A0). A2 is tied to GND; A0/A1 have a 4.7k pull-down
// and a solder jumper to 3V3: A0 = JP12, A1 = JP13 -> 0x38 with no jumper.
// ~INT has a 4.7k pull-up (R37) but is not wired to the ESP32: the switches are polled.
// ---------------------------------------------------------------------------
#define PCF_ADDR 0x38
#define PCF_INT_PIN -1 // not wired

static_assert(PCF_ADDR != PCA_1_ADDR && PCF_ADDR != PCA_2_ADDR && PCF_ADDR != 0x70,
              "The PCF8574 shares its I2C address with a PCA9685, check the solder jumpers");

// Switch contact to GND. The PCF8574 pins are quasi-bidirectional: write 1 to a pin
// (weak internal pull-up, 0xFF at power-on) before reading it; a closed switch reads 0.
// P0..P2 are not connected.
#define SWITCH_COUNT 5
const uint8_t SWITCH_PCF_BIT[SWITCH_COUNT] = {7, 6, 5, 4, 3}; // switch1..switch5 -> P7..P3

// ---------------------------------------------------------------------------
// TFT screen (J1, SPI, no reset line on the schematic, backlight "led" tied to 3V3)
// ---------------------------------------------------------------------------
#define TFT_MISO_PIN 10 // "sdo"
#define TFT_MOSI_PIN 12 // "sdi"
#define TFT_SCK_PIN 11  // "sck"
#define TFT_DC_PIN 13   // "dc"
#define TFT_CS_PIN 14   // "cs"

// ---------------------------------------------------------------------------
// Inputs on the ESP32 (contact to GND, no external pull-up: use INPUT_PULLUP)
// ---------------------------------------------------------------------------
#define TIRETTE_PIN 21  // starting cord, "tir"
#define BUTTON_1_PIN 48 // push button "Button1", "bu 1". Also drives the DevKitC-1 v1.0 onboard RGB LED
#define BUTTON_2_PIN 47 // push button "Button2", "bu 2"

// ---------------------------------------------------------------------------
// LIDAR LD06 (J5) on UART1. UART0 (GPIO43/44) stays free for the Serial logs.
// The Arduino default pins of Serial1 on the S3 are RX 15 / TX 16, i.e. PCA_OE and
// I2C SCL on this board: always pass the pins, Serial1.begin(LD06_BAUDRATE, SERIAL_8N1,
// LD06_RX_PIN, LD06_TX_PIN), and never call LD06::init(), which uses the defaults.
// ---------------------------------------------------------------------------
#define LD06_UART_NUM 1
#define LD06_RX_PIN 8 // ESP32 RX <- LD06 TX (J5 pin 3)
#define LD06_TX_PIN 9 // ESP32 TX -> LD06 RX (J5 pin 2)
#define LD06_BAUDRATE 230400
#define LD06_PWM_PIN 18 // motor speed PWM, J5 pin 5
